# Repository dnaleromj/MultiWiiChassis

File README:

MultiWiiChassis is a quad/hex flight control board and power distribution board that is meant to act as an electronics platform and a chassis at the same time.
Compatible with MultiWii and Aeroquad.
45mm standard spacing.

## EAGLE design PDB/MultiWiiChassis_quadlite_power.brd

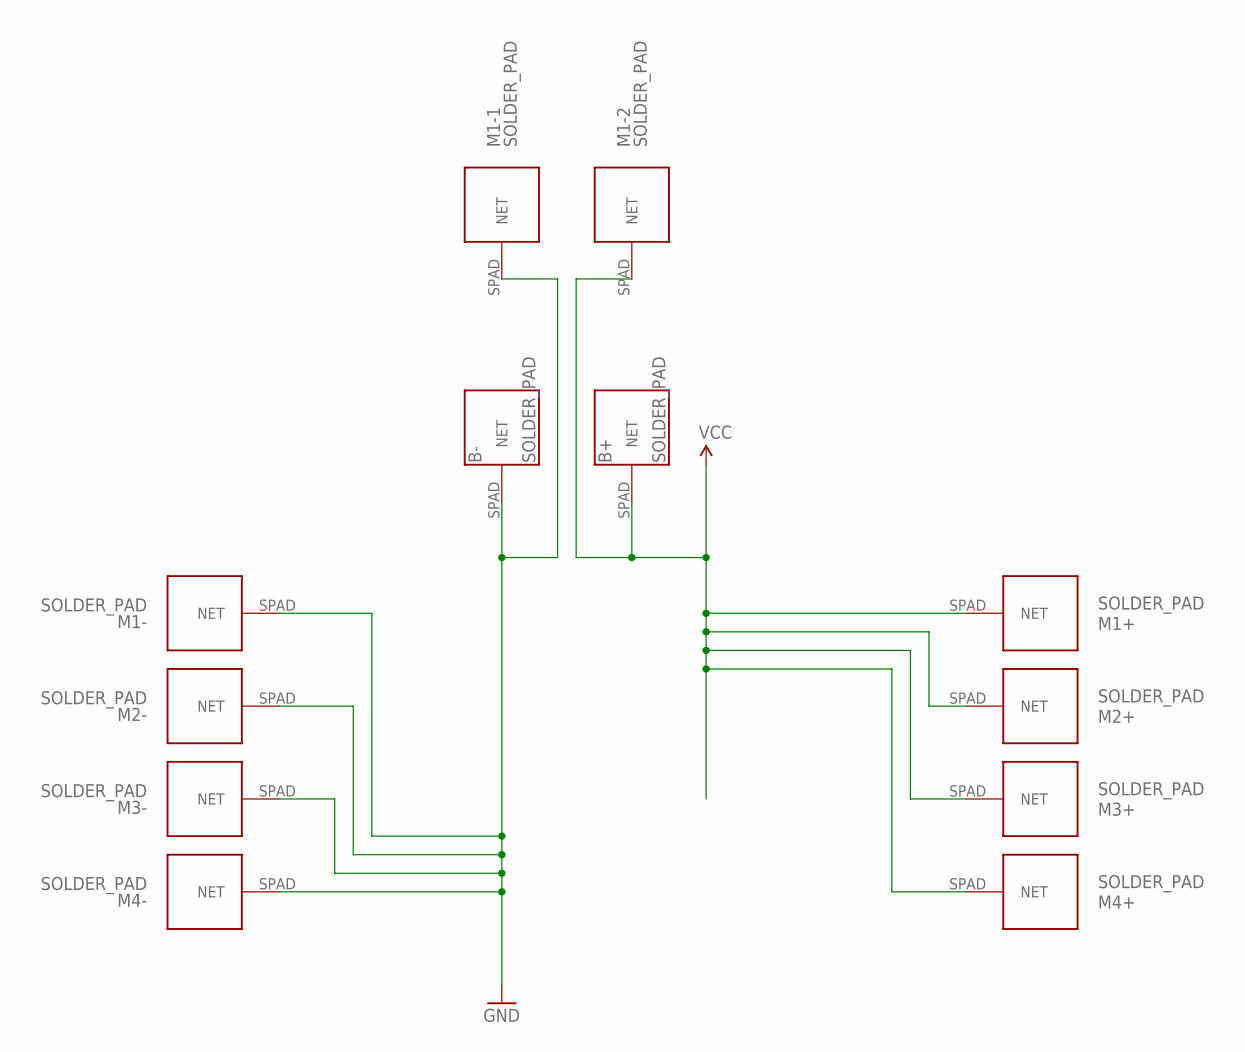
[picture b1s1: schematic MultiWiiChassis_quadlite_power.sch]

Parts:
B+: SOLDER_PAD
B-: SOLDER_PAD
M1+, M1-, M1-1, M1-2, M2+, M2-, M3+, M3-, M4+, M4-: SOLDER_PAD

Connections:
GND: B-.SPAD, M1-.SPAD, M1-1.SPAD, M2-.SPAD, M3-.SPAD, M4-.SPAD
VCC: B+.SPAD, M1+.SPAD, M1-2.SPAD, M2+.SPAD, M3+.SPAD, M4+.SPAD

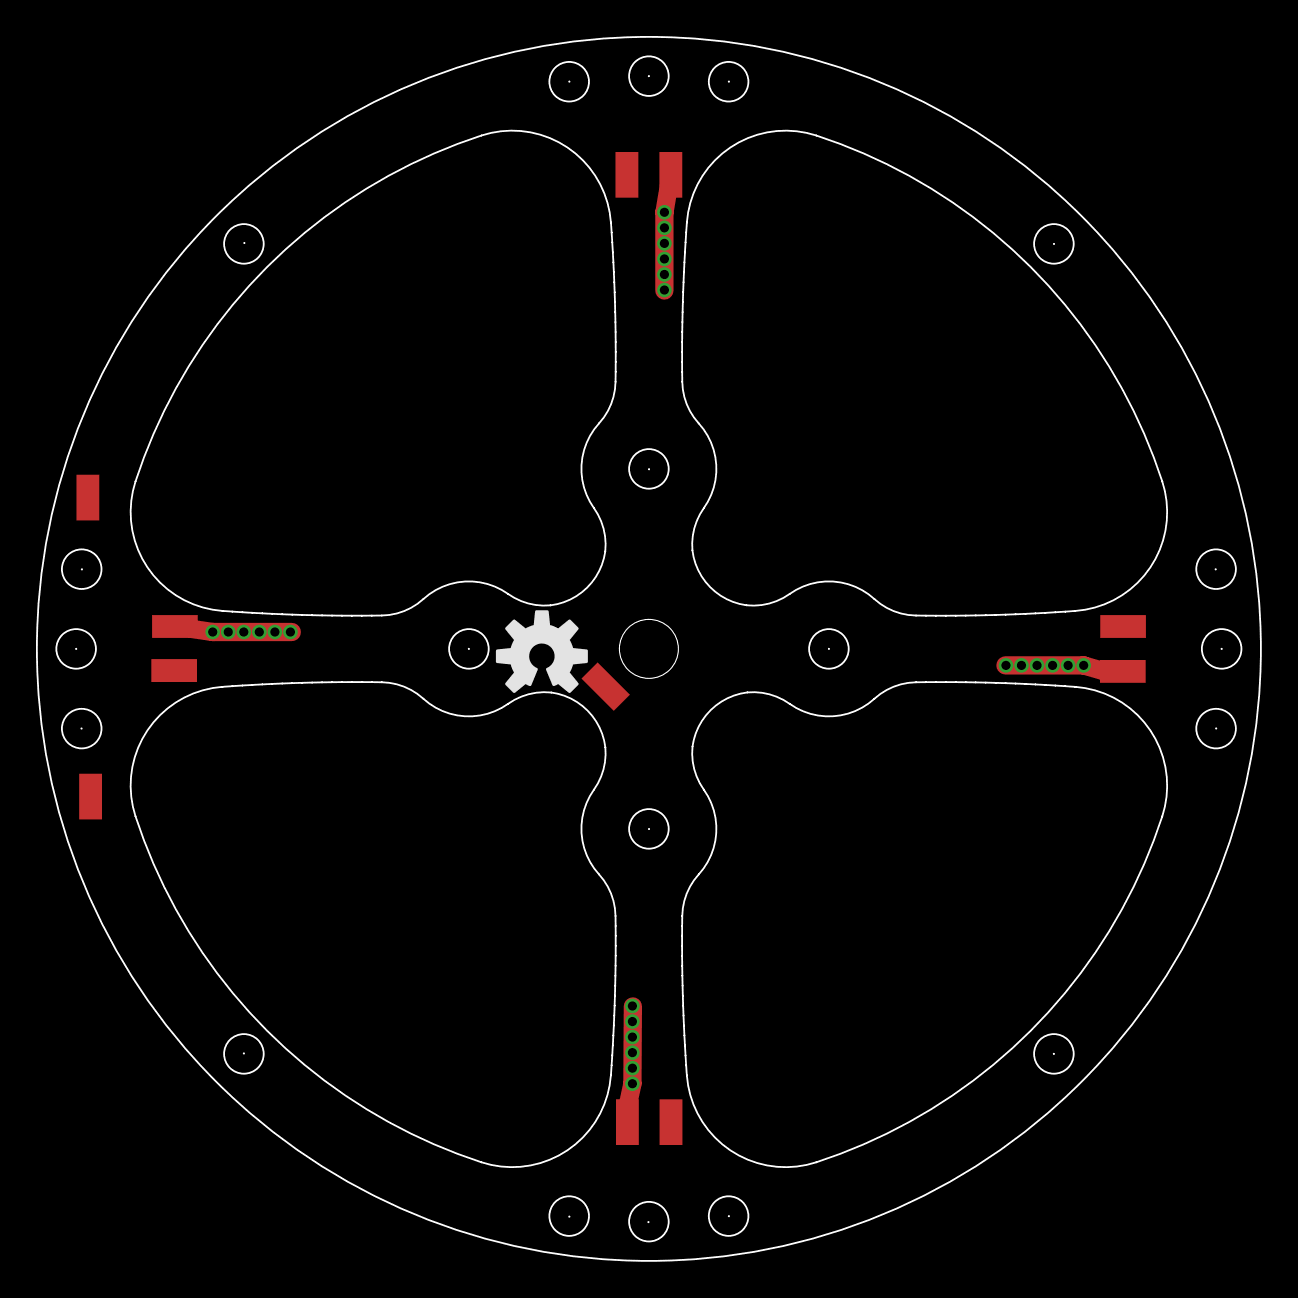
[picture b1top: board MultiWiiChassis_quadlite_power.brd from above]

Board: 2 copper layers, 68.0 x 68.0 mm, 13 parts (1 on the bottom side), 2 nets.

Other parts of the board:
U$2: OSHW-LOGO-M

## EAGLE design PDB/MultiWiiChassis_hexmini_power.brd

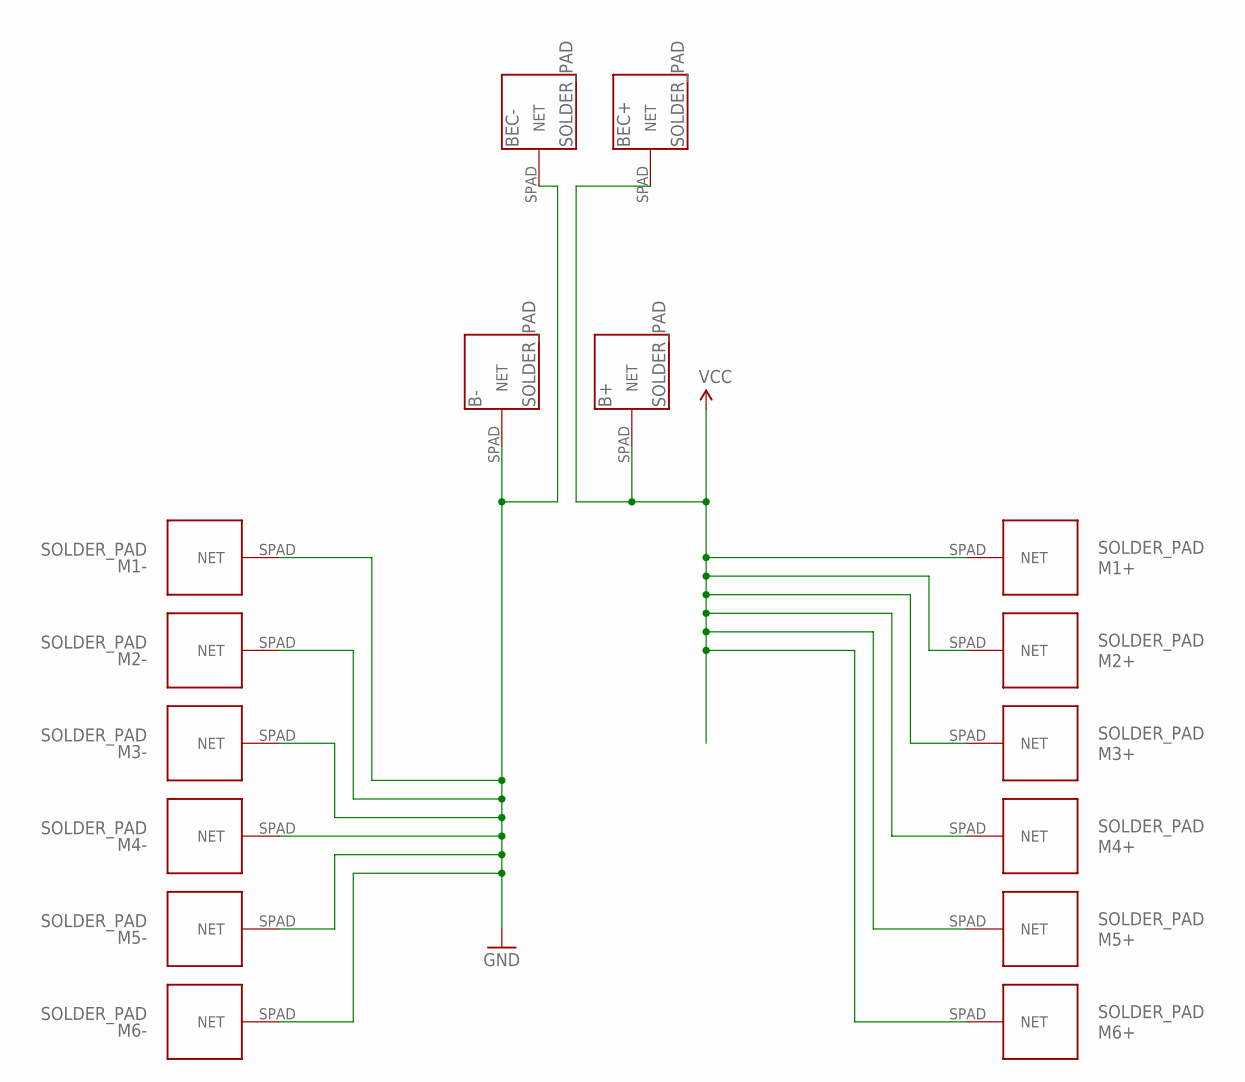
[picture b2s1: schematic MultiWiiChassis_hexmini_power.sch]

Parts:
B+: SOLDER_PAD
B-: SOLDER_PAD
BEC+: SOLDER_PAD
BEC-: SOLDER_PAD
M1+, M1-, M2+, M2-, M3+, M3-, M4+, M4-, M5+, M5-, M6+, M6-: SOLDER_PAD

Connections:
GND: B-.SPAD, BEC-.SPAD, M1-.SPAD, M2-.SPAD, M3-.SPAD, M4-.SPAD, M5-.SPAD, M6-.SPAD
VCC: B+.SPAD, BEC+.SPAD, M1+.SPAD, M2+.SPAD, M3+.SPAD, M4+.SPAD, M5+.SPAD, M6+.SPAD

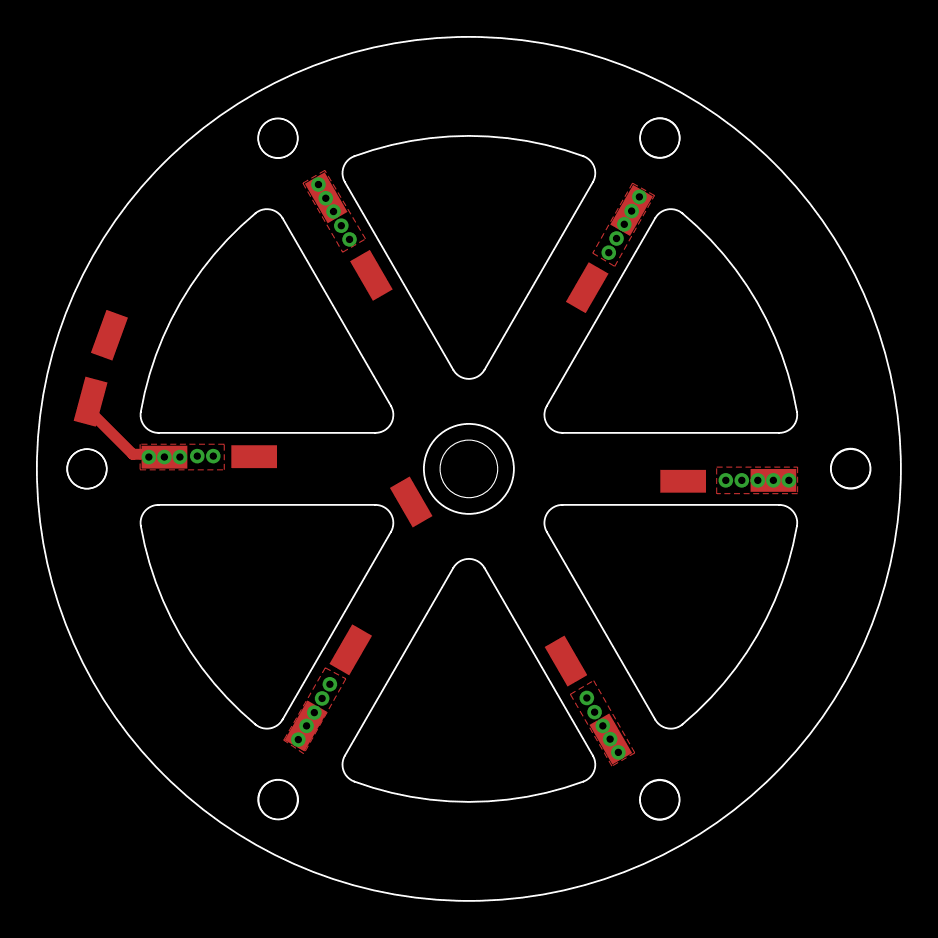
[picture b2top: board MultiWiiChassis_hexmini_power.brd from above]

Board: 2 copper layers, 48.0 x 48.0 mm, 16 parts (1 on the bottom side), 2 nets.

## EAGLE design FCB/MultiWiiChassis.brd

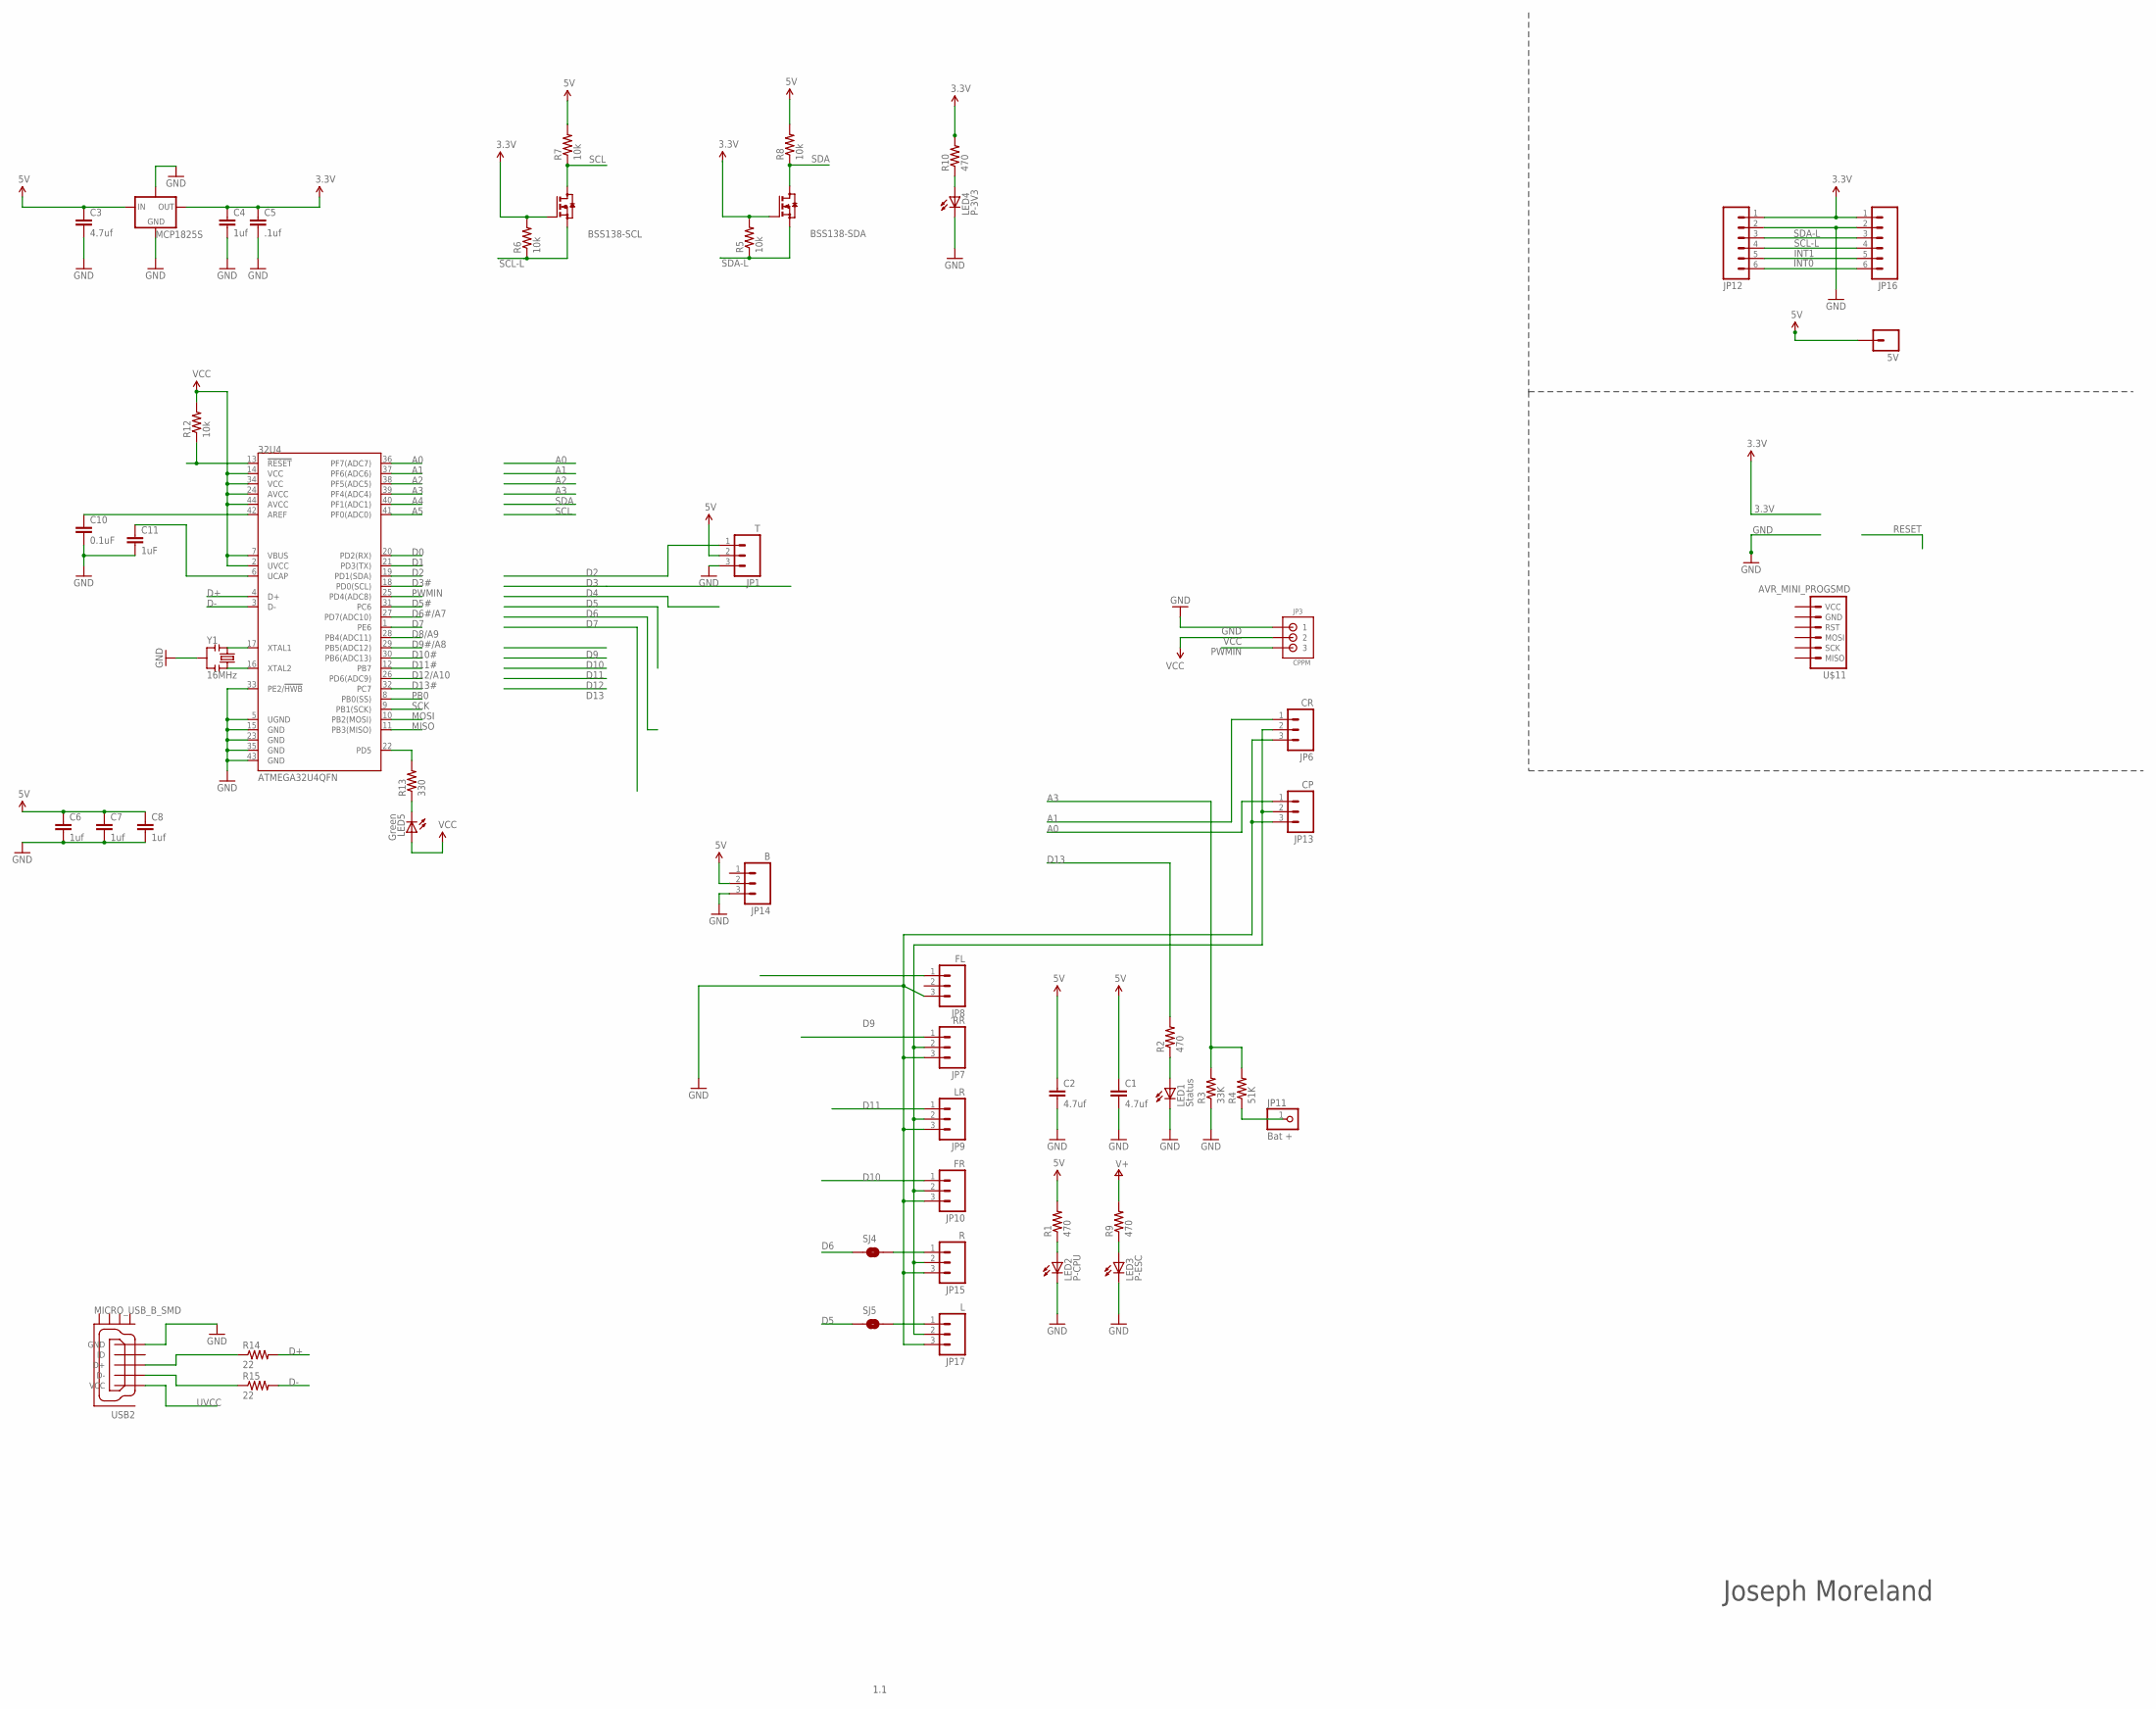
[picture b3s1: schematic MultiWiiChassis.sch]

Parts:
5V: M01PTH; 1X01
32U4: ATMEGA32U4QFN; SPARKFUN-DIGITALIC_QFN-44; PARTNO ATMEGA32U4-MU
BSS138-SCL, BSS138-SDA: BSS138BOTTOM; SOT23_BOT
C1, C2, C3: 4.7uf; 0603-CAP
C4, C6, C7, C8: 1uf; 0603-CAP
C5: .1uf; 0603-CAP
C10: 0.1uF; 0603-CAP; PARTNO C0603C104K8RACTU
C11: 1uF; 0402-CAP; PARTNO LMK105BJ105KV-F
JP1: T; 1X03
JP3: CPPM; B3B-ZR; PARTNO M20-9990346
JP6: CR; 1X03
JP7: RR; 1X03
JP8: FL; 1X03
JP9: LR; 1X03
JP10: FR; 1X03
JP11: Bat +; 1X01
JP12, JP16: M06LOCK; 1X06_LOCK
JP13: CP; 1X03
JP14: B; 1X03
JP15: R; 1X03
JP17: L; 1X03
LED1: Status; LED-1206
LED2: P-CPU; LED-1206
LED3: P-ESC; LED-1206
LED4: P-3V3; LED-1206
LED5: Green; LED-0603; PARTNO LTST-C190KGKT
MCP1825S: V_REG_MCP1825S; SOT223_BOT
R1, R2: 470; 0603-RES
R3: 33K; 0603-RES
R4: 51K; 0805
R5, R6, R7, R8: 10k; 0805
R9, R10: 470; 0805
R12: 10k; 0402-RES; PARTNO CRCW040210K0FKED
R13: 330; 0402-RES; PARTNO CRCW0402330RJNED
R14, R15: 22; 0402-RES; PARTNO CRCW040222R0JNED
SJ4, SJ5: SOLDERJUMPERNO; SJ_2S-NO
U$11: AVR_MINI_PROGSMD; AVR_MINI_PROG
USB2: MICRO_USB_B_SMD; MOLEX_MICRO_USB_B_BOTTOM_MOUNT; PARTNO 473460001
Y1: 16MHz; RESONATOR-SMD; PARTNO CSTCE16M0V53-R0

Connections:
3.3V: BSS138-SCL.G, BSS138-SDA.G, C4.1, C5.1, JP12.1, JP16.1, MCP1825S.3 (OUT), R5.2, R6.2, R10.2
5V: 5V.1, C1.1, C2.1, C3.1, C6.1, C7.1, C8.1, JP1.2, JP14.2, MCP1825S.1 (IN), R1.2, R7.2, R8.2
A0: 32U4.36 (PF7(ADC7)), JP13.1
A1: 32U4.37 (PF6(ADC6)), JP6.1
A2: 32U4.38 (PF5(ADC5))
A3: 32U4.39 (PF4(ADC4)), R3.2, R4.2
A4: 32U4.40 (PF1(ADC1))
A5: 32U4.41 (PF0(ADC0))
AREF1: 32U4.42 (AREF), C10.1
D0: 32U4.20 (PD2(RX))
D1: 32U4.21 (PD3(TX))
D2: 32U4.19 (PD1(SDA)), JP1.1
D3: JP8.1
D3#: 32U4.18 (PD0(SCL))
D5: SJ5.1
D5#: 32U4.31 (PC6)
D6: SJ4.1
D6#/A7: 32U4.27 (PD7(ADC10))
D7: 32U4.1 (PE6)
D8/A9: 32U4.28 (PB4(ADC11))
D9: JP7.1
D9#/A8: 32U4.29 (PB5(ADC12))
D10: JP10.1
D10#: 32U4.30 (PB6(ADC13))
D11: JP9.1
D11#: 32U4.12 (PB7)
D12/A10: 32U4.26 (PD6(ADC9))
D13: R2.2
D13#: 32U4.32 (PC7)
D+: 32U4.4 (D+), R14.2
D-: 32U4.3 (D-), R15.2
GND: 32U4.5 (UGND), 32U4.15 (GND), 32U4.23 (GND), 32U4.33 (PE2/!HWB), 32U4.35 (GND), 32U4.43 (GND), C1.2, C2.2, C3.2, C4.2, C5.2, C6.2, C7.2, C8.2, C10.2, C11.2, JP1.3, JP3.1, JP6.3, JP7.3, JP8.3, JP9.3, JP10.3, JP12.2, JP13.3, JP14.3, JP15.3, JP16.2, JP17.3, LED1.C, LED2.C, LED3.C, LED4.C, MCP1825S.2 (GND), MCP1825S.GNDPAD, R3.1, USB2.5 (GND), Y1.2
INT0: JP12.6, JP16.6
INT1: JP12.5, JP16.5
MISO: 32U4.11 (PB3(MISO))
MOSI: 32U4.10 (PB2(MOSI))
unnamed: LED1.A, R2.1
unnamed: LED2.A, R1.1
unnamed: JP11.1, R4.1
unnamed: 32U4.17 (XTAL1), Y1.1
unnamed: 32U4.16 (XTAL2), Y1.3
unnamed: R14.1, USB2.3 (D+)
unnamed: LED5.C, R13.1
unnamed: JP15.1, SJ4.2
unnamed: R15.1, USB2.2 (D-)
unnamed: LED4.A, R10.1
unnamed: LED3.A, R9.1
unnamed: JP17.1, SJ5.2
unnamed: 32U4.22 (PD5), R13.2
PB0: 32U4.8 (PB0(SS))
PWMIN: 32U4.25 (PD4(ADC8)), JP3.3
RESET1: 32U4.13 (!RESET), R12.1
SCK: 32U4.9 (PB1(SCK))
SCL: BSS138-SCL.D, R7.1
SCL-L: BSS138-SCL.S, JP12.4, JP16.4, R6.1
SDA: BSS138-SDA.D, R8.1
SDA-L: BSS138-SDA.S, JP12.3, JP16.3, R5.1
UCAP: 32U4.6 (UCAP), C11.1
UVCC: USB2.1 (VCC)
VCC: 32U4.2 (UVCC), 32U4.7 (VBUS), 32U4.14 (VCC), 32U4.24 (AVCC), 32U4.34 (VCC), 32U4.44 (AVCC), JP3.2, LED5.A, R12.2
VESC: JP6.2, JP7.2, JP9.2, JP10.2, JP13.2, JP15.2, JP17.2, R9.2

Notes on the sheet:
1.1
Joseph Moreland

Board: 2 copper layers, 53 parts (3 on the bottom side), 34 nets, no tracks yet.

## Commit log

2011-09-23 Initial Setup
2011-09-23 Initial commit of eagle files
2011-09-23 commited 1.2 eagle files
2011-09-24 Restructure
2011-10-02 Upped to v1.3
2011-10-02 Added 3v3 led status light. Added solder jumpers to allow for arduino pin reuse between motor control pins and receiver control pins
2011-10-02 Added readme
2011-10-02 Added power status LED and created hex board
2011-10-02 removed version numbers from PCBs
2013-04-16 Added power boards for hexa and quad, nano and standard + povray.
2013-04-16 gerbers generated, unchecked

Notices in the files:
parts and their libraries:
SparkFun-Aesthetics: Licensing: CC v3.0 Share-Alike You are welcome to use this library for commercial purposes.
